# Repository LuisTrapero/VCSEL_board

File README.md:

# VCSEL Board

PCB designed to connect the Optilab VCSEL 1550nm to the driver CLD1015 from Thorlabs.

 - Optilabs VCSEL 1550nm: www.optilab.com/devices/category/vcsel/SM_1550_nm_VCSEL_pigtail_with_2.5_Gbps/
 - CLD1015 driver: https://www.thorlabs.com/thorproduct.cfm?partnumber=CLD1015#ad-image-0

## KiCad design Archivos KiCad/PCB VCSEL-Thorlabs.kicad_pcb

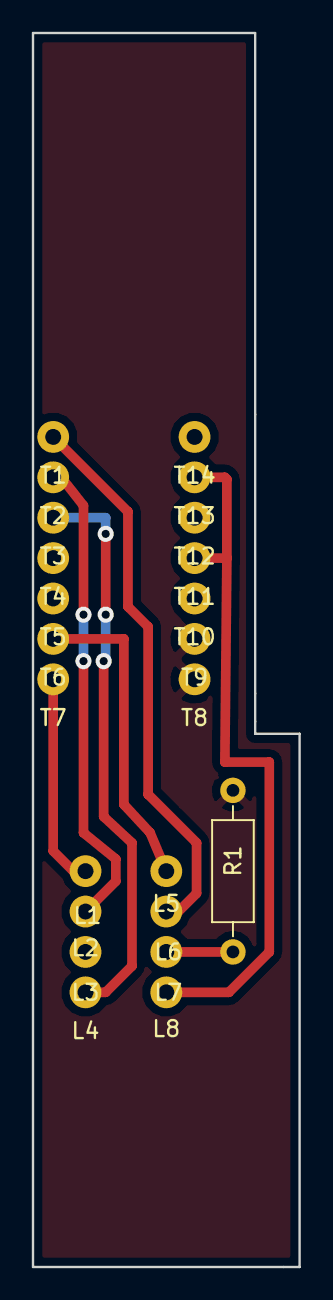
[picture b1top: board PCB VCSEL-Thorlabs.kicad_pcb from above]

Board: 2 copper layers, 16.8 x 77.6 mm, 23 parts (0 on the bottom side), 8 nets.

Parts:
L1: TEC Cath; TaladroVCSEL
L2: Therm; TaladroVCSEL
L3: NA; TaladroVCSEL
L4: VCSEL Cath; TaladroVCSEL
L5: TEC Anode; TaladroVCSEL
L6: Therm2; TaladroVCSEL
L7: PD Cath; TaladroVCSEL
L8: VCSEL Anode; TaladroVCSEL
R1: R; R_Axial_DIN0207_L6.3mm_D2.5mm_P10.16mm_Horizontal
T1: Therm1; TaladroThorlabs
T2: Therm2; TaladroThorlabs
T3: LDCath; TaladroThorlabs
T4: PDAnode; TaladroThorlabs
T5: PDCath; TaladroThorlabs
T6: TEC+; TaladroThorlabs
T7: TEC-; TaladroThorlabs
T8, T9: GND; TaladroThorlabs
T10, T12, T14: NC; TaladroThorlabs
T11, T13: LDAnode; TaladroThorlabs

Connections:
GND: R1.1, T8.1, T9.1
unnamed: L1.1, T7.1
unnamed: L2.1, T2.1
unnamed: L4.1, T3.1
unnamed: L5.1, T6.1
unnamed: L6.1, T1.1
unnamed: L7.1, R1.2
unnamed: L8.1, T11.1, T13.1

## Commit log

2017-09-10 Imported KiCad files
